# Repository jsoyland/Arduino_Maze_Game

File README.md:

# Arduino Maze Game

We thought that it might be fun to make a "video game console" out of an Arduino and decided on a maze game.  

### Console
The design for the console was hand-drawn and then reproduced in OpenSCAD.

### Wiring 

We used a ILI9341 320x240 screen and an Arudino Nano.  Initially it only showed a white screen, but it tuns out that all its inputs require to be 3.3V, which meant we needed a 3.3V-5V logic level converter in between the Arduino and the screen.  With that in place, the wiring looks like:
|Display | Arduino |
| ----- | ----- |
| VCC | 3v3 |
| GND | GND | 
| CS | 10 | 
| RESET | 3v3 | 
| DC | 9 | 
| SDI(MOSI) | 11 | 
| SCK | 13|  
| LED | 3v3 | 
| SDO(MISO) | 12 | 
| T_CLK | 13 |
| T_CS | 8 |
| T_DIN | 11 |
| T_DO | 12 |
| T_IRQ | not connected |

We aren't using any of the touch capabilities here, though I went ahead and wired it up.  I don't totally understand it but Arduno has an ["SPI" interface](https://www.arduino.cc/reference/en/language/functions/communication/spi/) that the touchscreen and display devices both use.  The Output/Input/Clock pins are shared between the two peripherals, which the Chip Select is different (here it's pins 10 and 8).

Also wired up a joystick to control the maze:
| Thumbstick | Arduino |
| SW | 2 |
| VRY | A0 |
| VRX | A1 |
| +5V | 5V |
| GND | GND |

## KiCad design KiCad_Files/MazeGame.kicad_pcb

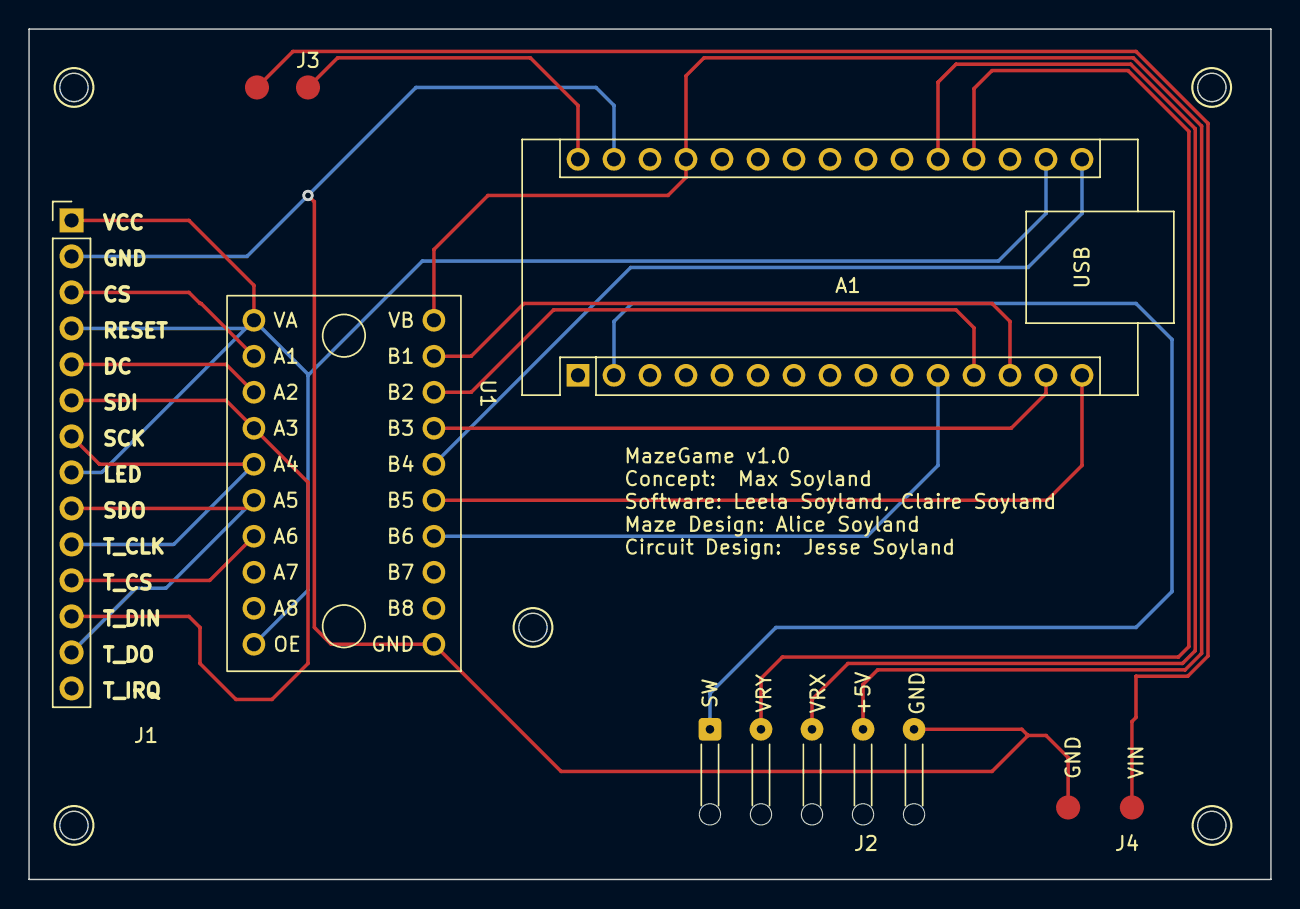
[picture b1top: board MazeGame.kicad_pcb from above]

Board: 2 copper layers, 87.6 x 60.0 mm, 6 parts (0 on the bottom side), 20 nets.

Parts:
A1: Arduino_Nano_v3.x; Arduino_Nano
J1: ILI9341; PinHeader_1x14_P2.54mm_Vertical
J2: Thumbstick; SolderWire-0.1sqmm_1x05_P3.6mm_D0.4mm_OD1mm_Relief
J3: Switch; SolderWire-0.1sqmm_1x02_P3.6mm_D0.4mm_OD1mm
J4: Power; SolderWire-0.25sqmm_1x02_P4.5mm_D0.65mm_OD2mm
U1: EPLZON_TXS0108E; EPLZON TXS0108E Board

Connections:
unnamed: A1.11 (D8), U1.7 (B6)
unnamed: A1.14 (D11), U1.4 (B3)
unnamed: A1.15 (D12), U1.6 (B5)
unnamed: A1.16 (D13), U1.5 (B4)
unnamed: A1.17 (3V3), J1.1 (VCC), J1.4 (RESET), J1.8 (LED), U1.11 (VA), U1.20 (OE)
unnamed: J1.3 (CS), U1.12 (A1)
unnamed: J1.5 (DC), U1.13 (A2)
unnamed: J1.6 (SDI), J1.12 (T_DIN), U1.14 (A3)
unnamed: J1.7 (SCK), J1.10 (T_CLK), U1.15 (A4)
unnamed: A1.2 (D0/RX), J2.1
unnamed: A1.19 (A0), J2.2
unnamed: A1.20 (A1), J2.3
unnamed: A1.27 (+5V), J2.4, U1.1 (VB)
unnamed: A1.29 (GND), J1.2 (GND), J2.5, J4.2, U1.10 (GND)
unnamed: A1.30 (VIN), J3.1
unnamed: J3.2, J4.1
unnamed: A1.13 (D10), U1.2 (B1)
unnamed: A1.12 (D9), U1.3 (B2)
unnamed: J1.9 (SDO), J1.13 (T_DO), U1.16 (A5)
unnamed: J1.11 (T_CS), U1.17 (A6)

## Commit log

2022-10-12 Init
2022-10-12 Widen thumbstick hole a bit
2022-10-12 Widen top for mounting screen
2022-10-13 Slice in half, add interior space
2022-10-13 Rounded corners on display hole
2022-10-15 Add screw holes for screen
2022-10-15 Add barrier for battery
2022-10-15 Add hole for battery cord
2022-10-15 Shorten handle by 5mm
2022-10-16 Screen standoffs reduce to 3.43mm
2022-10-16 Mounting block for thumbstick
2022-10-16 Grouping adds/subtracts, fix indents
2022-10-16 Screw holes for body halves
2022-10-16 Reduce size of thumbstick mounts
2022-10-17 Minor cosmetic adjustments
2022-10-17 Weird fix for 'valid 2-manifold' error
2022-10-17 Reduce roundness of interior volume
2022-10-17 screen mounting blocks 1mm further apart
2022-10-17 screen mounting blocks .5mm shorter
2022-10-18 screen mounting blocks - adjustment
2022-10-19 Mounting post for circuit board. Cylinders
2022-10-19 Parameterize circuit board standoff
2022-10-19 move thumbstick hole 2mm down
2022-10-19 ignore .DS_Store 🤦🏻‍
2022-10-19 Add 1mm to spacing of circuit standoffs
2022-10-19 Convert thumbstick blocks to cylinders
2022-10-20 Add hole for switch
2022-10-20 Adjust position of battery wire hole
2022-10-20 Rotating arduino board 90°
2022-10-24 Add USB_C Hole
2022-10-24 Single larger board vs two
2022-10-24 Make mount posts a little thicker
2022-10-26 Dimensional adjustments after test print
2022-10-26 USB-C Port Adjustment
2022-11-27 Update with touchscreen and joystick wirings
2022-11-27 Minor updates
2022-11-27 Drawing mode uses full screen now
2022-11-27 Add KiCad circuit diagram and layout
2022-11-28 Adjust circuit standoffs for new PCB
2022-11-28 Move USB-C port to align better with new PCB
2022-11-29 Thumbstick mods for PCB.
2022-11-29 Adjust circuit standoffs
2022-11-29 Change pin for thumbstick button
    I originally had D2 in the code and tested with that. When making
    the circuit board accidentally used "pin 2" which was RX0.
    In a stroke of luck it turns out that RX0 can be initialized as
    a digital input (D0), so changed to use that instead.
2022-11-30 Trying cylinders for body mounts
2022-11-30 Move USB-C hole down 2mm
2022-11-30 Adjust circuit board mount holes
